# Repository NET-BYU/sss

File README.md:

# Seven Segment Sign

## Welcome to the Seven Segment Sign! (SSS)

## Getting Started
Here are some helpful links to get you up and running!
- [API Docs](https://sss.readthedocs.io/en/latest/API/Display/)
- [Install on Linux/Mac](https://sss.readthedocs.io/en/latest/Installation/Install%20SSS%20on%20Mac%20or%20Linux/)
- [Install on Windows](https://sss.readthedocs.io/en/latest/Installation/Install%20SSS%20on%20Windows/)
- [Create your first demo](https://sss.readthedocs.io/en/latest/Tutorials/Creating%20a%20demo/)

## Common Commands
Although thorough information on how to [get started](https://sss.readthedocs.io/en/latest/Overview/Get%20started/) is in the docs, here are some quick commands you can run in order to get rolling **once you have everything installed**:

- Run the PyGame Simulator for the SSS
  ```bash
  python3 main.py simulator
  ```
- Run a specific demo in the simulator
  ```bash
  python3 main.py demo <demo_name> -s
  ```
- Start the SSS in kiosk mode
  ```bash
  python3 main.py kiosk
  ```
- To view log output of varying degrees, use the `-v` option (the more `v`'s the more `v`erbose the output becomes

For any other help or a list of comprehensive commands, run
```bash
python3 main.py --help
```

## Reporting an Issue
We love feedback! As the SSS codespace expands and acquires new features, we realize that some bugs will fall through the cracks. Please feel free to open a new issue if you notice any bugs in the code, mistakes or missing information in the documentation, or if you want a new feature to be added to the project.

You can go to the **Issues** tab to create a new issue. Please be mindful to choose the correct template for the right type of question. Apart from the currently open issues from before this writing, any **issue that does not conform to the template may become stale or be closed without warning.**

## Submitting a PR
If you are feeling creative and you would like to contribute a demo but you are outside of our organization, you are more than welcome to submit a pull request and we will look it over! 

In order for a pull request to be merged, we have the following three policies:
1. Your code must have adequate, meaningful comments. Don't feel like you have to explain every statement, but also don't write comments like `# This a loop that goes over all the values`.
2. Your PR will need approval from **at least 2 org members**. Users who respond to these the most are @apal6981, @christopolise, and @philipbl
3. Your code **MUST** be formatted with `black`. This is as simple as adding the [Black Formatter](https://marketplace.visualstudio.com/items?itemName=ms-python.black-formatter) to VS/OSS Code or running `python3 -m black <your py files>`

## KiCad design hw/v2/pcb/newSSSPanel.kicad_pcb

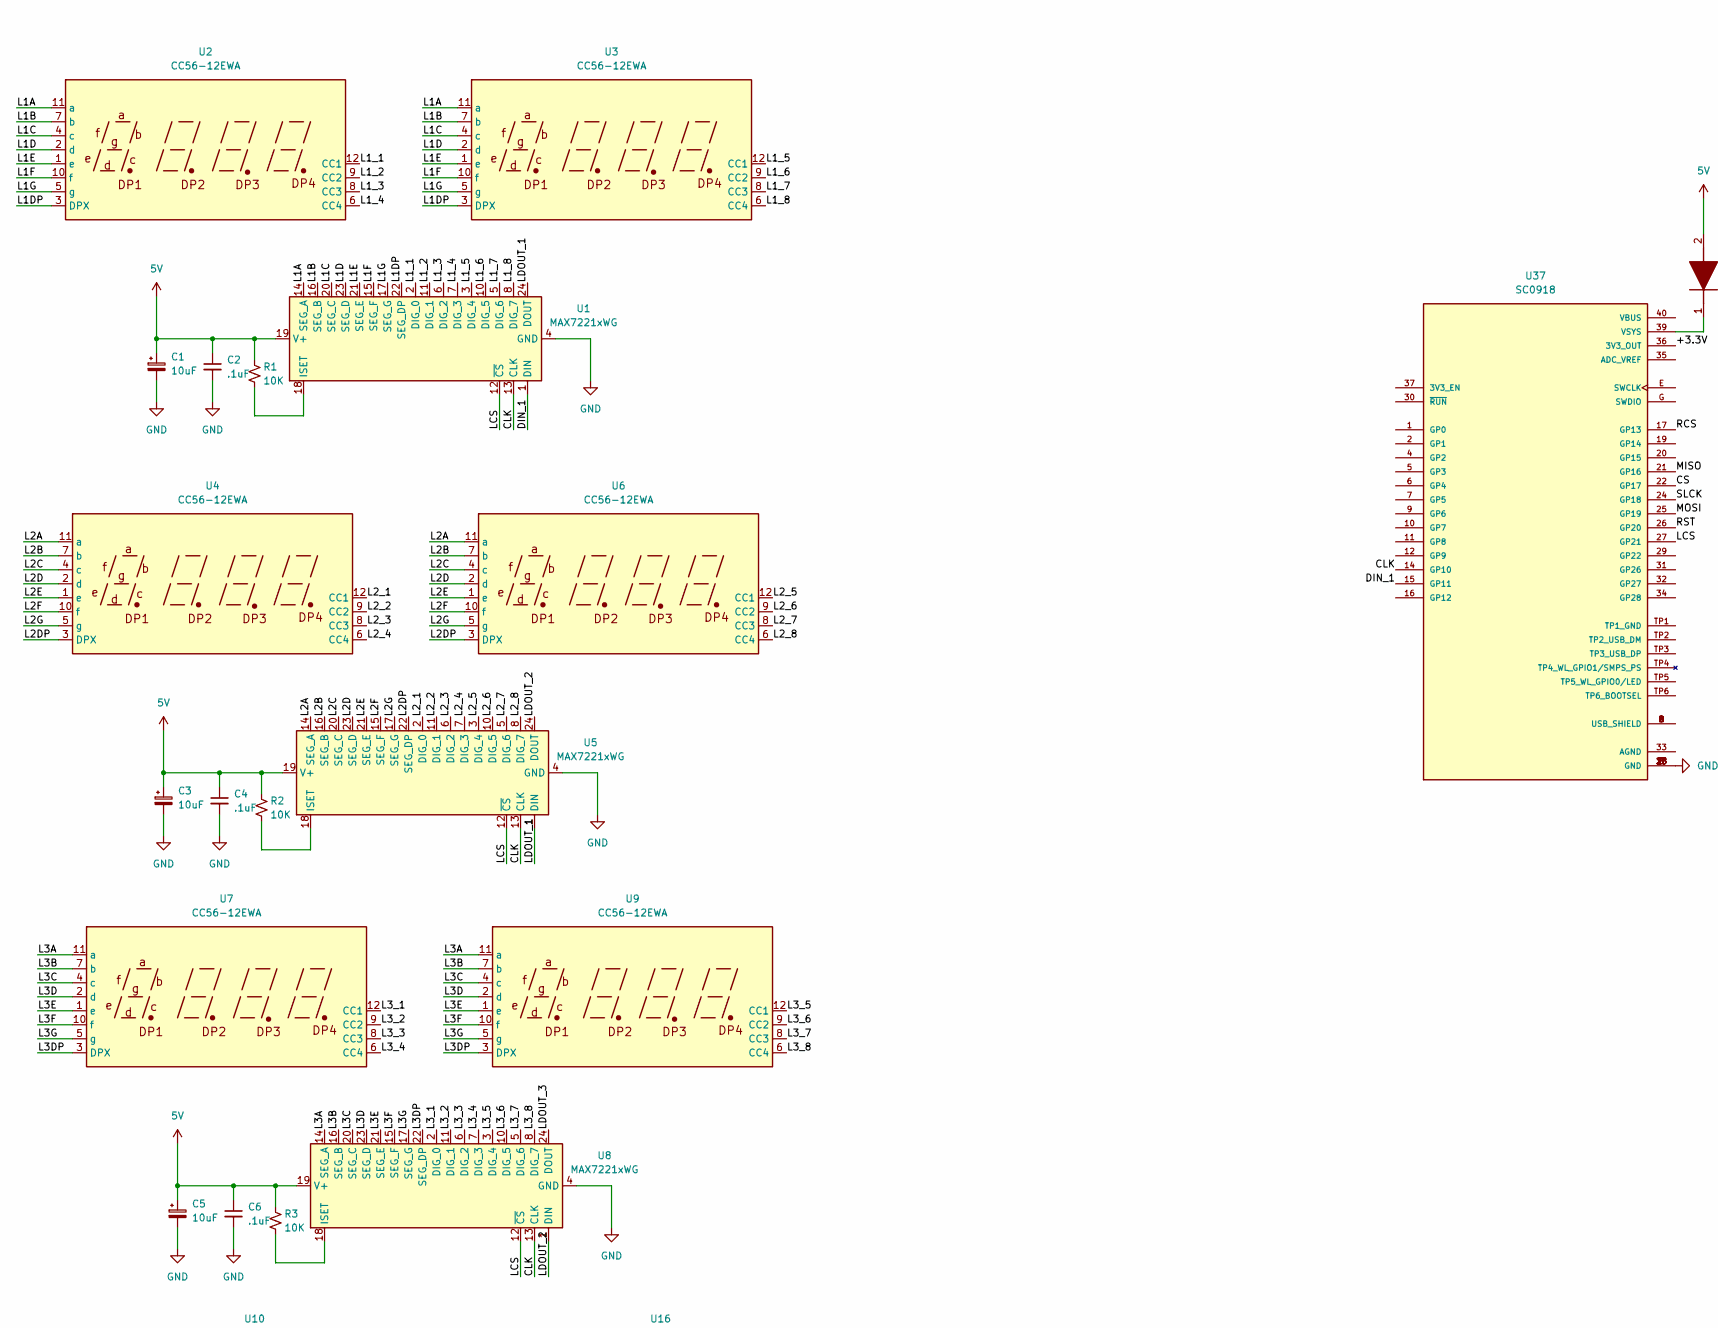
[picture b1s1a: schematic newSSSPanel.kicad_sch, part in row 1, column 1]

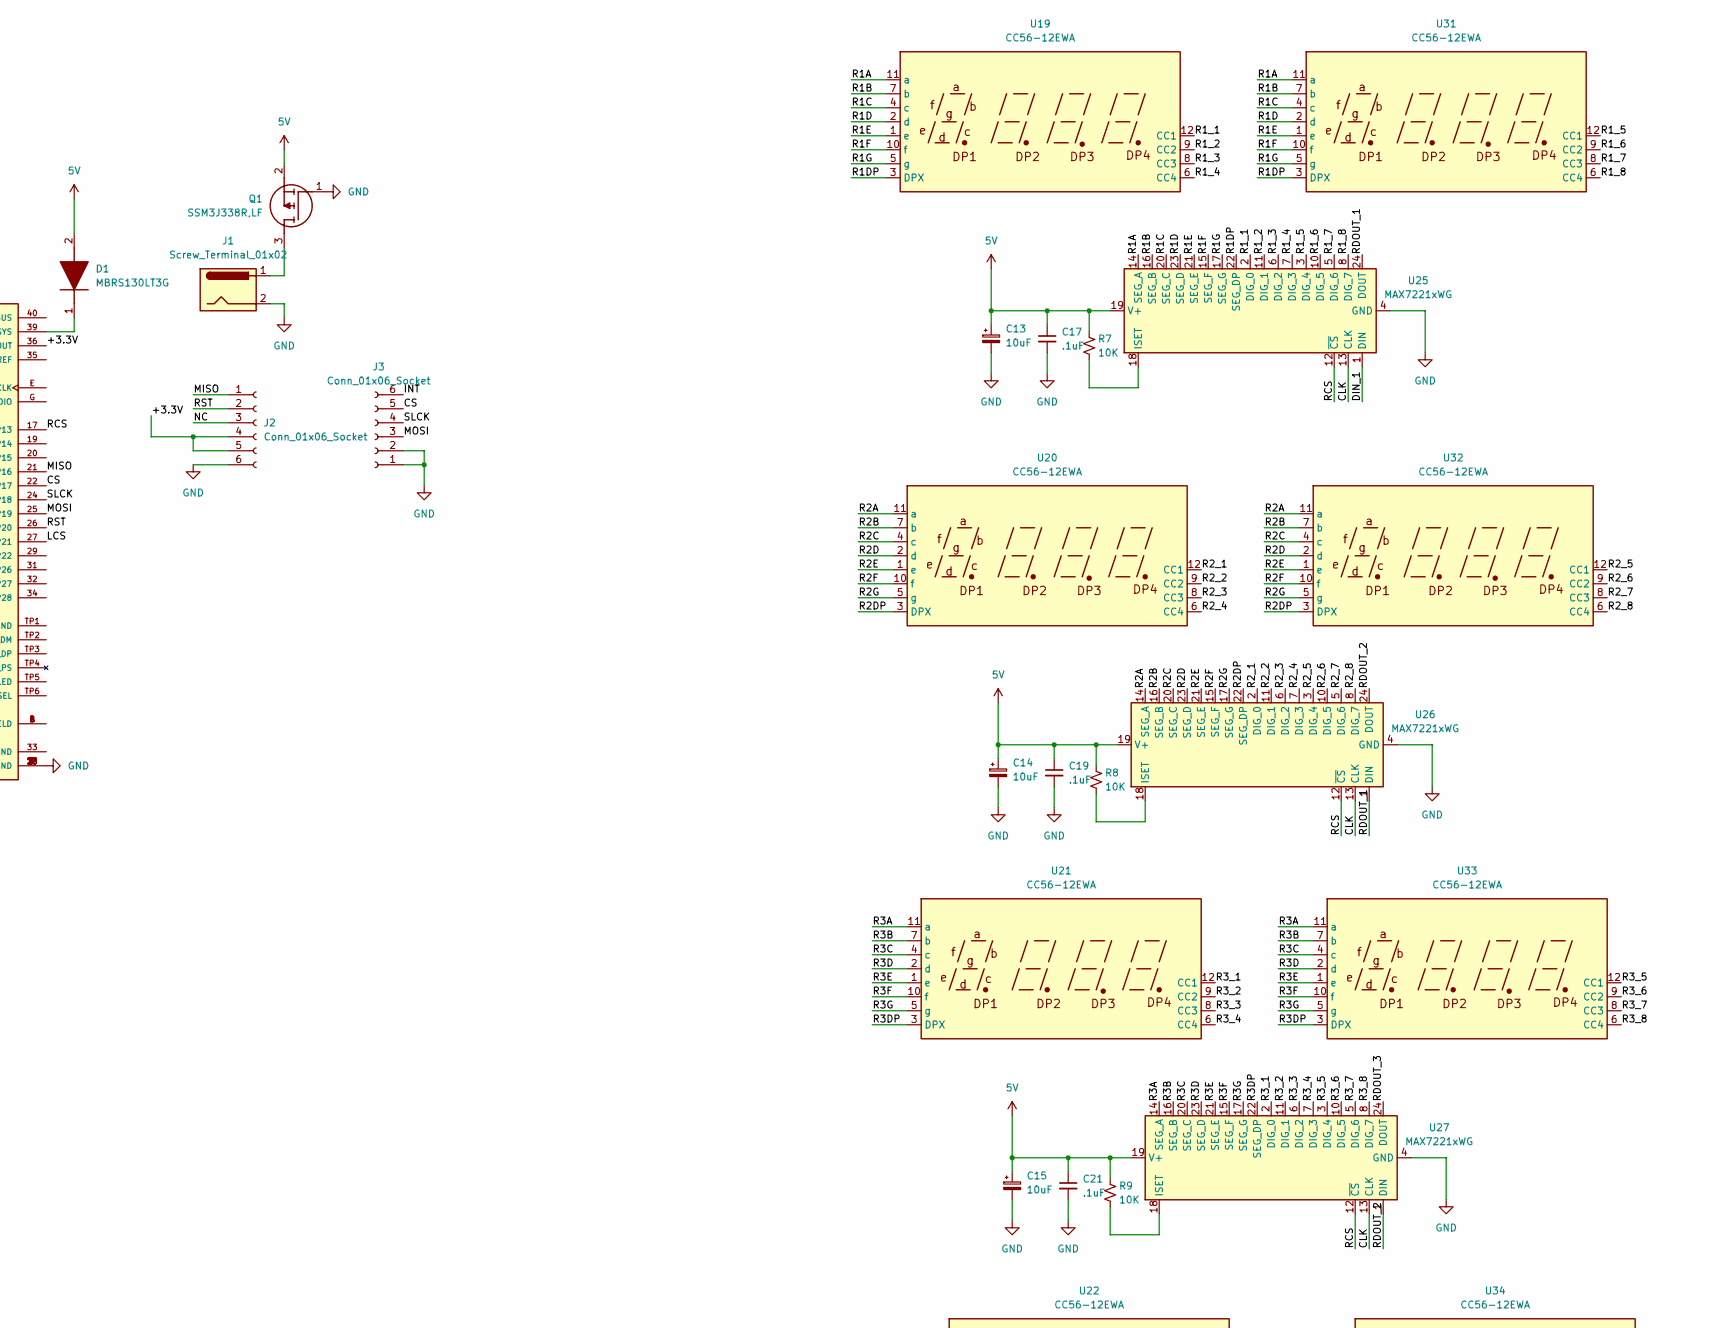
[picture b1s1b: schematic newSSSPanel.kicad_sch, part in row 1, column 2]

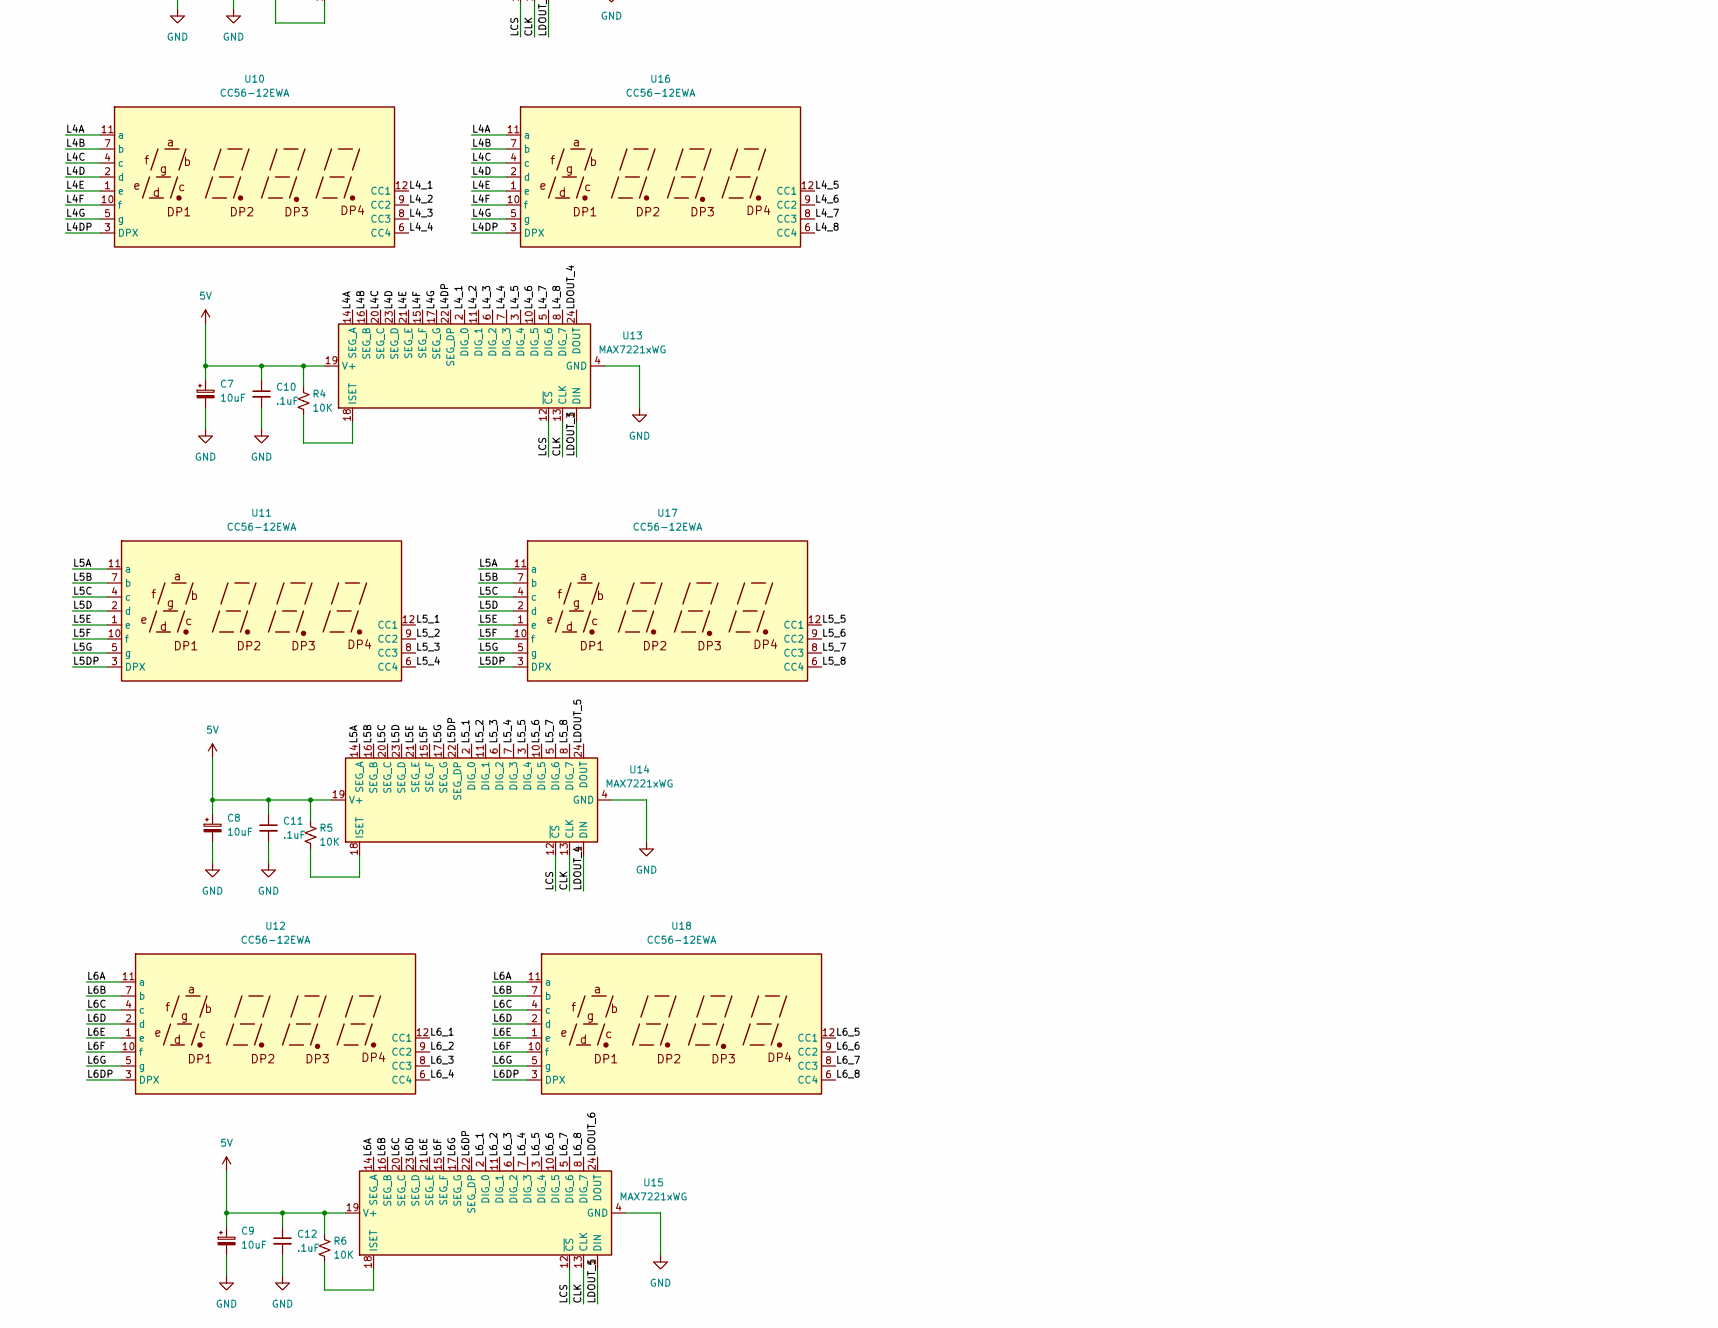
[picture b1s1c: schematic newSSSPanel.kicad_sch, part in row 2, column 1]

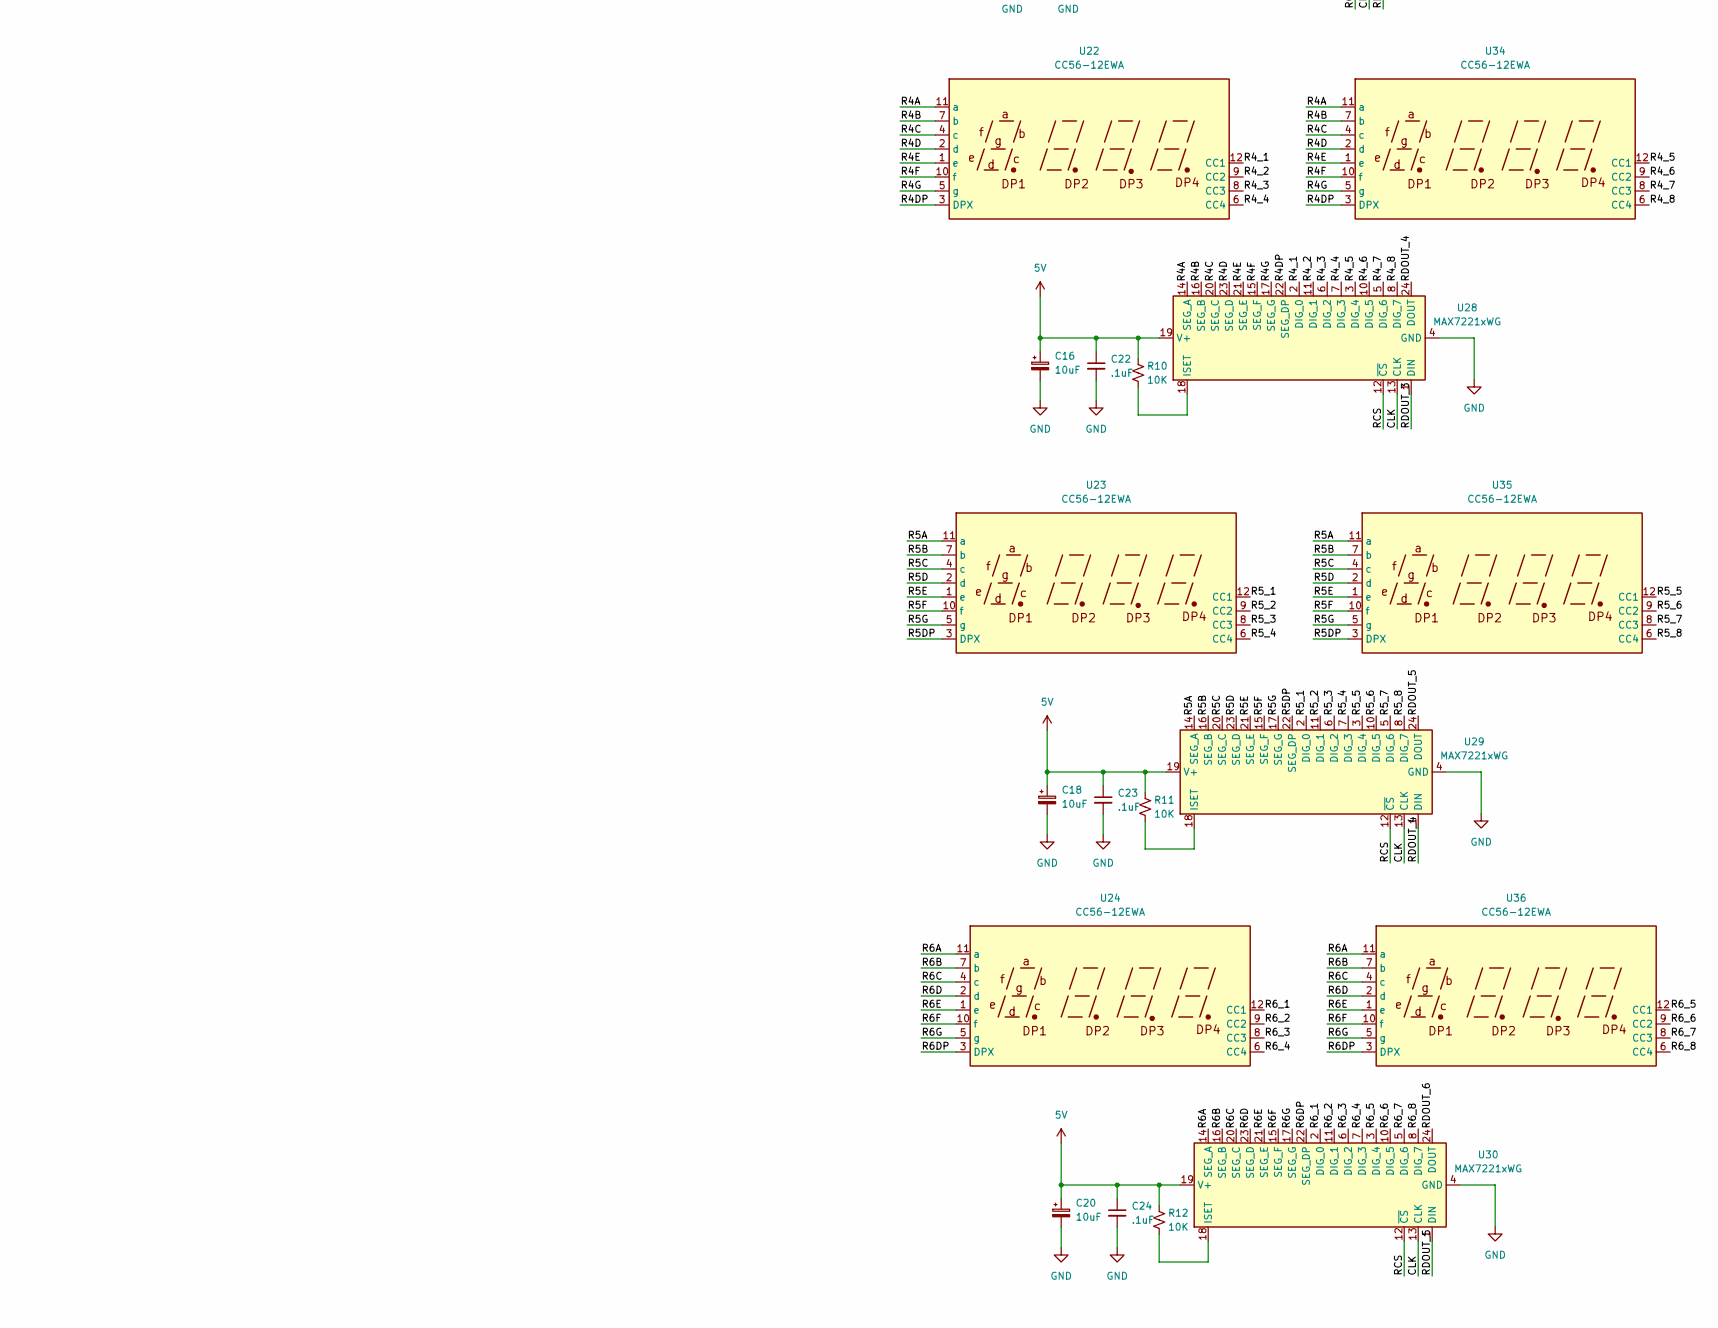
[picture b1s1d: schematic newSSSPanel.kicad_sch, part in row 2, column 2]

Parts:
C1, C3, C5, C7, C8, C9, C13, C14, C15, C16, C18, C20: 10uF; CP_Elec_3x5.4
C2, C4, C6, C10, C11, C12, C17, C19, C21, C22, C23, C24: .1uF; C_0805_2012Metric_Pad1.18x1.45mm_HandSolder
D1: MBRS130LT3G; DIOM5436X247N; Mouser Part Number 863-MBRS130LT3G
J1: Screw_Terminal_01x02; BarrelJack_Horizontal
J2, J3: Conn_01x06_Socket; PinHeader_1x06_P2.54mm_Vertical
Q1: SSM3J338R,LF; SSM3J332RLFT; Mouser Part Number 757-SSM3J338RLF
R1, R2, R3, R4, R5, R6, R7, R8, R9, R10, R11, R12: 10K; R_0805_2012Metric_Pad1.20x1.40mm_HandSolder
U1, U5, U8, U13, U14, U15, U25, U26, U27, U28, U29, U30: MAX7221xWG; SOIC-24W_7.5x15.4mm_P1.27mm
U2, U3, U4, U6, U7, U9, U10, U11, U12, U16, U17, U18, U19, U20, U21, U22, U23, U24, U31, U32, U33, U34, U35, U36: CC56-12EWA; CA56-12EWA
U37: SC0918; MODULE_SC0918; PARTREV 2.1

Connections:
5V: C1.1, C2.1, C3.1, C4.1, C5.1, C6.1, C7.1, C8.1, C9.1, C10.1, C11.1, C12.1, C13.1, C14.1, C15.1, C16.1, C17.1, C18.1, C19.1, C20.1, C21.1, C22.1, C23.1, C24.1, D1.2 (A), Q1.2 (S), R1.1, R2.1, R3.1, R4.1, R5.1, R6.1, R7.1, R8.1, R9.1, R10.1, R11.1, R12.1, U1.19 (V+), U5.19 (V+), U8.19 (V+), U13.19 (V+), U14.19 (V+), U15.19 (V+), U25.19 (V+), U26.19 (V+), U27.19 (V+), U28.19 (V+), U29.19 (V+), U30.19 (V+)
/+3.3V: J2.4, J2.5, U37.36 (3V3_OUT)
/CLK: U1.13 (CLK), U5.13 (CLK), U8.13 (CLK), U13.13 (CLK), U14.13 (CLK), U15.13 (CLK), U25.13 (CLK), U26.13 (CLK), U27.13 (CLK), U28.13 (CLK), U29.13 (CLK), U30.13 (CLK), U37.14 (GP10)
/CS: J3.5, U37.22 (GP17)
/DIN_1: U1.1 (DIN), U25.1 (DIN), U37.15 (GP11)
/INT: J3.6
/L1A: U1.14 (SEG_A), U2.11 (a), U3.11 (a)
/L1B: U1.16 (SEG_B), U2.7 (b), U3.7 (b)
/L1C: U1.20 (SEG_C), U2.4 (c), U3.4 (c)
/L1D: U1.23 (SEG_D), U2.2 (d), U3.2 (d)
/L1DP: U1.22 (SEG_DP), U2.3 (DPX), U3.3 (DPX)
/L1E: U1.21 (SEG_E), U2.1 (e), U3.1 (e)
/L1F: U1.15 (SEG_F), U2.10 (f), U3.10 (f)
/L1G: U1.17 (SEG_G), U2.5 (g), U3.5 (g)
/L1_1: U1.2 (DIG_0), U2.12 (CC1)
/L1_2: U1.11 (DIG_1), U2.9 (CC2)
/L1_3: U1.6 (DIG_2), U2.8 (CC3)
/L1_4: U1.7 (DIG_3), U2.6 (CC4)
/L1_5: U1.3 (DIG_4), U3.12 (CC1)
/L1_6: U1.10 (DIG_5), U3.9 (CC2)
/L1_7: U1.5 (DIG_6), U3.8 (CC3)
/L1_8: U1.8 (DIG_7), U3.6 (CC4)
/L2A: U4.11 (a), U5.14 (SEG_A), U6.11 (a)
/L2B: U4.7 (b), U5.16 (SEG_B), U6.7 (b)
/L2C: U4.4 (c), U5.20 (SEG_C), U6.4 (c)
/L2D: U4.2 (d), U5.23 (SEG_D), U6.2 (d)
/L2DP: U4.3 (DPX), U5.22 (SEG_DP), U6.3 (DPX)
/L2E: U4.1 (e), U5.21 (SEG_E), U6.1 (e)
/L2F: U4.10 (f), U5.15 (SEG_F), U6.10 (f)
/L2G: U4.5 (g), U5.17 (SEG_G), U6.5 (g)
/L2_1: U4.12 (CC1), U5.2 (DIG_0)
/L2_2: U4.9 (CC2), U5.11 (DIG_1)
/L2_3: U4.8 (CC3), U5.6 (DIG_2)
/L2_4: U4.6 (CC4), U5.7 (DIG_3)
/L2_5: U5.3 (DIG_4), U6.12 (CC1)
/L2_6: U5.10 (DIG_5), U6.9 (CC2)
/L2_7: U5.5 (DIG_6), U6.8 (CC3)
/L2_8: U5.8 (DIG_7), U6.6 (CC4)
/L3A: U7.11 (a), U8.14 (SEG_A), U9.11 (a)
/L3B: U7.7 (b), U8.16 (SEG_B), U9.7 (b)
/L3C: U7.4 (c), U8.20 (SEG_C), U9.4 (c)
/L3D: U7.2 (d), U8.23 (SEG_D), U9.2 (d)
/L3DP: U7.3 (DPX), U8.22 (SEG_DP), U9.3 (DPX)
/L3E: U7.1 (e), U8.21 (SEG_E), U9.1 (e)
/L3F: U7.10 (f), U8.15 (SEG_F), U9.10 (f)
/L3G: U7.5 (g), U8.17 (SEG_G), U9.5 (g)
/L3_1: U7.12 (CC1), U8.2 (DIG_0)
/L3_2: U7.9 (CC2), U8.11 (DIG_1)
/L3_3: U7.8 (CC3), U8.6 (DIG_2)
/L3_4: U7.6 (CC4), U8.7 (DIG_3)
/L3_5: U8.3 (DIG_4), U9.12 (CC1)
/L3_6: U8.10 (DIG_5), U9.9 (CC2)
/L3_7: U8.5 (DIG_6), U9.8 (CC3)
/L3_8: U8.8 (DIG_7), U9.6 (CC4)
/L4A: U10.11 (a), U13.14 (SEG_A), U16.11 (a)
/L4B: U10.7 (b), U13.16 (SEG_B), U16.7 (b)
/L4C: U10.4 (c), U13.20 (SEG_C), U16.4 (c)
/L4D: U10.2 (d), U13.23 (SEG_D), U16.2 (d)
/L4DP: U10.3 (DPX), U13.22 (SEG_DP), U16.3 (DPX)
/L4E: U10.1 (e), U13.21 (SEG_E), U16.1 (e)
/L4F: U10.10 (f), U13.15 (SEG_F), U16.10 (f)
/L4G: U10.5 (g), U13.17 (SEG_G), U16.5 (g)
/L4_1: U10.12 (CC1), U13.2 (DIG_0)
/L4_2: U10.9 (CC2), U13.11 (DIG_1)
/L4_3: U10.8 (CC3), U13.6 (DIG_2)
/L4_4: U10.6 (CC4), U13.7 (DIG_3)
/L4_5: U13.3 (DIG_4), U16.12 (CC1)
/L4_6: U13.10 (DIG_5), U16.9 (CC2)
/L4_7: U13.5 (DIG_6), U16.8 (CC3)
/L4_8: U13.8 (DIG_7), U16.6 (CC4)
/L5A: U11.11 (a), U14.14 (SEG_A), U17.11 (a)
/L5B: U11.7 (b), U14.16 (SEG_B), U17.7 (b)
/L5C: U11.4 (c), U14.20 (SEG_C), U17.4 (c)
/L5D: U11.2 (d), U14.23 (SEG_D), U17.2 (d)
/L5DP: U11.3 (DPX), U14.22 (SEG_DP), U17.3 (DPX)
/L5E: U11.1 (e), U14.21 (SEG_E), U17.1 (e)
/L5F: U11.10 (f), U14.15 (SEG_F), U17.10 (f)
/L5G: U11.5 (g), U14.17 (SEG_G), U17.5 (g)
/L5_1: U11.12 (CC1), U14.2 (DIG_0)
/L5_2: U11.9 (CC2), U14.11 (DIG_1)
/L5_3: U11.8 (CC3), U14.6 (DIG_2)
/L5_4: U11.6 (CC4), U14.7 (DIG_3)
/L5_5: U14.3 (DIG_4), U17.12 (CC1)
/L5_6: U14.10 (DIG_5), U17.9 (CC2)
/L5_7: U14.5 (DIG_6), U17.8 (CC3)
/L5_8: U14.8 (DIG_7), U17.6 (CC4)
/L6A: U12.11 (a), U15.14 (SEG_A), U18.11 (a)
/L6B: U12.7 (b), U15.16 (SEG_B), U18.7 (b)
/L6C: U12.4 (c), U15.20 (SEG_C), U18.4 (c)
/L6D: U12.2 (d), U15.23 (SEG_D), U18.2 (d)
/L6DP: U12.3 (DPX), U15.22 (SEG_DP), U18.3 (DPX)
/L6E: U12.1 (e), U15.21 (SEG_E), U18.1 (e)
/L6F: U12.10 (f), U15.15 (SEG_F), U18.10 (f)
/L6G: U12.5 (g), U15.17 (SEG_G), U18.5 (g)
/L6_1: U12.12 (CC1), U15.2 (DIG_0)
/L6_2: U12.9 (CC2), U15.11 (DIG_1)
/L6_3: U12.8 (CC3), U15.6 (DIG_2)
/L6_4: U12.6 (CC4), U15.7 (DIG_3)
/L6_5: U15.3 (DIG_4), U18.12 (CC1)
/L6_6: U15.10 (DIG_5), U18.9 (CC2)
/L6_7: U15.5 (DIG_6), U18.8 (CC3)
/L6_8: U15.8 (DIG_7), U18.6 (CC4)
/LCS: U1.12 (~CS), U5.12 (~CS), U8.12 (~CS), U13.12 (~CS), U14.12 (~CS), U15.12 (~CS), U37.27 (GP21)
/LDOUT_1: U1.24 (DOUT), U5.1 (DIN)
/LDOUT_2: U5.24 (DOUT), U8.1 (DIN)
/LDOUT_3: U8.24 (DOUT), U13.1 (DIN)
/LDOUT_4: U13.24 (DOUT), U14.1 (DIN)
/LDOUT_5: U14.24 (DOUT), U15.1 (DIN)
/LDOUT_6: U15.24 (DOUT)
/MISO: J2.1, U37.21 (GP16)
/MOSI: J3.3, U37.25 (GP19)
/NC: J2.3
/R1A: U19.11 (a), U25.14 (SEG_A), U31.11 (a)
/R1B: U19.7 (b), U25.16 (SEG_B), U31.7 (b)
/R1C: U19.4 (c), U25.20 (SEG_C), U31.4 (c)
/R1D: U19.2 (d), U25.23 (SEG_D), U31.2 (d)
/R1DP: U19.3 (DPX), U25.22 (SEG_DP), U31.3 (DPX)
/R1E: U19.1 (e), U25.21 (SEG_E), U31.1 (e)
/R1F: U19.10 (f), U25.15 (SEG_F), U31.10 (f)
/R1G: U19.5 (g), U25.17 (SEG_G), U31.5 (g)
/R1_1: U19.12 (CC1), U25.2 (DIG_0)
/R1_2: U19.9 (CC2), U25.11 (DIG_1)
/R1_3: U19.8 (CC3), U25.6 (DIG_2)
/R1_4: U19.6 (CC4), U25.7 (DIG_3)
/R1_5: U25.3 (DIG_4), U31.12 (CC1)
/R1_6: U25.10 (DIG_5), U31.9 (CC2)
/R1_7: U25.5 (DIG_6), U31.8 (CC3)
/R1_8: U25.8 (DIG_7), U31.6 (CC4)
/R2A: U20.11 (a), U26.14 (SEG_A), U32.11 (a)
/R2B: U20.7 (b), U26.16 (SEG_B), U32.7 (b)
/R2C: U20.4 (c), U26.20 (SEG_C), U32.4 (c)
/R2D: U20.2 (d), U26.23 (SEG_D), U32.2 (d)
/R2DP: U20.3 (DPX), U26.22 (SEG_DP), U32.3 (DPX)
/R2E: U20.1 (e), U26.21 (SEG_E), U32.1 (e)
/R2F: U20.10 (f), U26.15 (SEG_F), U32.10 (f)
/R2G: U20.5 (g), U26.17 (SEG_G), U32.5 (g)
/R2_1: U20.12 (CC1), U26.2 (DIG_0)
/R2_2: U20.9 (CC2), U26.11 (DIG_1)
/R2_3: U20.8 (CC3), U26.6 (DIG_2)
/R2_4: U20.6 (CC4), U26.7 (DIG_3)
/R2_5: U26.3 (DIG_4), U32.12 (CC1)
/R2_6: U26.10 (DIG_5), U32.9 (CC2)
/R2_7: U26.5 (DIG_6), U32.8 (CC3)
/R2_8: U26.8 (DIG_7), U32.6 (CC4)
/R3A: U21.11 (a), U27.14 (SEG_A), U33.11 (a)
/R3B: U21.7 (b), U27.16 (SEG_B), U33.7 (b)
/R3C: U21.4 (c), U27.20 (SEG_C), U33.4 (c)
/R3D: U21.2 (d), U27.23 (SEG_D), U33.2 (d)
/R3DP: U21.3 (DPX), U27.22 (SEG_DP), U33.3 (DPX)
/R3E: U21.1 (e), U27.21 (SEG_E), U33.1 (e)
/R3F: U21.10 (f), U27.15 (SEG_F), U33.10 (f)
/R3G: U21.5 (g), U27.17 (SEG_G), U33.5 (g)
/R3_1: U21.12 (CC1), U27.2 (DIG_0)
/R3_2: U21.9 (CC2), U27.11 (DIG_1)
/R3_3: U21.8 (CC3), U27.6 (DIG_2)
/R3_4: U21.6 (CC4), U27.7 (DIG_3)
/R3_5: U27.3 (DIG_4), U33.12 (CC1)
/R3_6: U27.10 (DIG_5), U33.9 (CC2)
/R3_7: U27.5 (DIG_6), U33.8 (CC3)
/R3_8: U27.8 (DIG_7), U33.6 (CC4)
/R4A: U22.11 (a), U28.14 (SEG_A), U34.11 (a)
/R4B: U22.7 (b), U28.16 (SEG_B), U34.7 (b)
/R4C: U22.4 (c), U28.20 (SEG_C), U34.4 (c)
/R4D: U22.2 (d), U28.23 (SEG_D), U34.2 (d)
/R4DP: U22.3 (DPX), U28.22 (SEG_DP), U34.3 (DPX)
/R4E: U22.1 (e), U28.21 (SEG_E), U34.1 (e)
/R4F: U22.10 (f), U28.15 (SEG_F), U34.10 (f)
/R4G: U22.5 (g), U28.17 (SEG_G), U34.5 (g)
/R4_1: U22.12 (CC1), U28.2 (DIG_0)
/R4_2: U22.9 (CC2), U28.11 (DIG_1)
/R4_3: U22.8 (CC3), U28.6 (DIG_2)
/R4_4: U22.6 (CC4), U28.7 (DIG_3)
/R4_5: U28.3 (DIG_4), U34.12 (CC1)
/R4_6: U28.10 (DIG_5), U34.9 (CC2)
/R4_7: U28.5 (DIG_6), U34.8 (CC3)
/R4_8: U28.8 (DIG_7), U34.6 (CC4)
/R5A: U23.11 (a), U29.14 (SEG_A), U35.11 (a)
/R5B: U23.7 (b), U29.16 (SEG_B), U35.7 (b)
/R5C: U23.4 (c), U29.20 (SEG_C), U35.4 (c)
/R5D: U23.2 (d), U29.23 (SEG_D), U35.2 (d)
/R5DP: U23.3 (DPX), U29.22 (SEG_DP), U35.3 (DPX)
/R5E: U23.1 (e), U29.21 (SEG_E), U35.1 (e)
/R5F: U23.10 (f), U29.15 (SEG_F), U35.10 (f)
/R5G: U23.5 (g), U29.17 (SEG_G), U35.5 (g)
/R5_1: U23.12 (CC1), U29.2 (DIG_0)
/R5_2: U23.9 (CC2), U29.11 (DIG_1)
/R5_3: U23.8 (CC3), U29.6 (DIG_2)
/R5_4: U23.6 (CC4), U29.7 (DIG_3)
/R5_5: U29.3 (DIG_4), U35.12 (CC1)
/R5_6: U29.10 (DIG_5), U35.9 (CC2)
/R5_7: U29.5 (DIG_6), U35.8 (CC3)
/R5_8: U29.8 (DIG_7), U35.6 (CC4)
/R6A: U24.11 (a), U30.14 (SEG_A), U36.11 (a)
/R6B: U24.7 (b), U30.16 (SEG_B), U36.7 (b)
/R6C: U24.4 (c), U30.20 (SEG_C), U36.4 (c)
/R6D: U24.2 (d), U30.23 (SEG_D), U36.2 (d)
/R6DP: U24.3 (DPX), U30.22 (SEG_DP), U36.3 (DPX)
/R6E: U24.1 (e), U30.21 (SEG_E), U36.1 (e)
/R6F: U24.10 (f), U30.15 (SEG_F), U36.10 (f)
/R6G: U24.5 (g), U30.17 (SEG_G), U36.5 (g)
/R6_1: U24.12 (CC1), U30.2 (DIG_0)
/R6_2: U24.9 (CC2), U30.11 (DIG_1)
/R6_3: U24.8 (CC3), U30.6 (DIG_2)
/R6_4: U24.6 (CC4), U30.7 (DIG_3)
/R6_5: U30.3 (DIG_4), U36.12 (CC1)
/R6_6: U30.10 (DIG_5), U36.9 (CC2)
/R6_7: U30.5 (DIG_6), U36.8 (CC3)
/R6_8: U30.8 (DIG_7), U36.6 (CC4)
/RCS: U25.12 (~CS), U26.12 (~CS), U27.12 (~CS), U28.12 (~CS), U29.12 (~CS), U30.12 (~CS), U37.17 (GP13)
/RDOUT_1: U25.24 (DOUT), U26.1 (DIN)
/RDOUT_2: U26.24 (DOUT), U27.1 (DIN)
/RDOUT_3: U27.24 (DOUT), U28.1 (DIN)
/RDOUT_4: U28.24 (DOUT), U29.1 (DIN)
/RDOUT_5: U29.24 (DOUT), U30.1 (DIN)
/RDOUT_6: U30.24 (DOUT)
/RST: J2.2, U37.26 (GP20)
/SLCK: J3.4, U37.24 (GP18)
GND: C1.2, C2.2, C3.2, C4.2, C5.2, C6.2, C7.2, C8.2, C9.2, C10.2, C11.2, C12.2, C13.2, C14.2, C15.2, C16.2, C17.2, C18.2, C19.2, C20.2, C21.2, C22.2, C23.2, C24.2, J1.2, J2.6, J3.1, J3.2, Q1.1 (G), U1.4 (GND), U1.9 (GND), U5.4 (GND), U5.9 (GND), U8.4 (GND), U8.9 (GND), U13.4 (GND), U13.9 (GND), U14.4 (GND), U14.9 (GND), U15.4 (GND), U15.9 (GND), U25.4 (GND), U25.9 (GND), U26.4 (GND), U26.9 (GND), U27.4 (GND), U27.9 (GND), U28.4 (GND), U28.9 (GND), U29.4 (GND), U29.9 (GND), U30.4 (GND), U30.9 (GND), U37.3 (GND), U37.8 (GND), U37.13 (GND), U37.18 (GND), U37.23 (GND), U37.28 (GND), U37.38 (GND), U37.F (GND)
unnamed: D1.1 (K), U37.39 (VSYS)
unnamed: J1.1, Q1.3 (D)
unnamed: R1.2, U1.18 (ISET)
unnamed: R2.2, U5.18 (ISET)
unnamed: R3.2, U8.18 (ISET)
unnamed: R4.2, U13.18 (ISET)
unnamed: R5.2, U14.18 (ISET)
unnamed: R6.2, U15.18 (ISET)
unnamed: R7.2, U25.18 (ISET)
unnamed: R8.2, U26.18 (ISET)
unnamed: R9.2, U27.18 (ISET)
unnamed: R10.2, U28.18 (ISET)
unnamed: R11.2, U29.18 (ISET)
unnamed: R12.2, U30.18 (ISET)

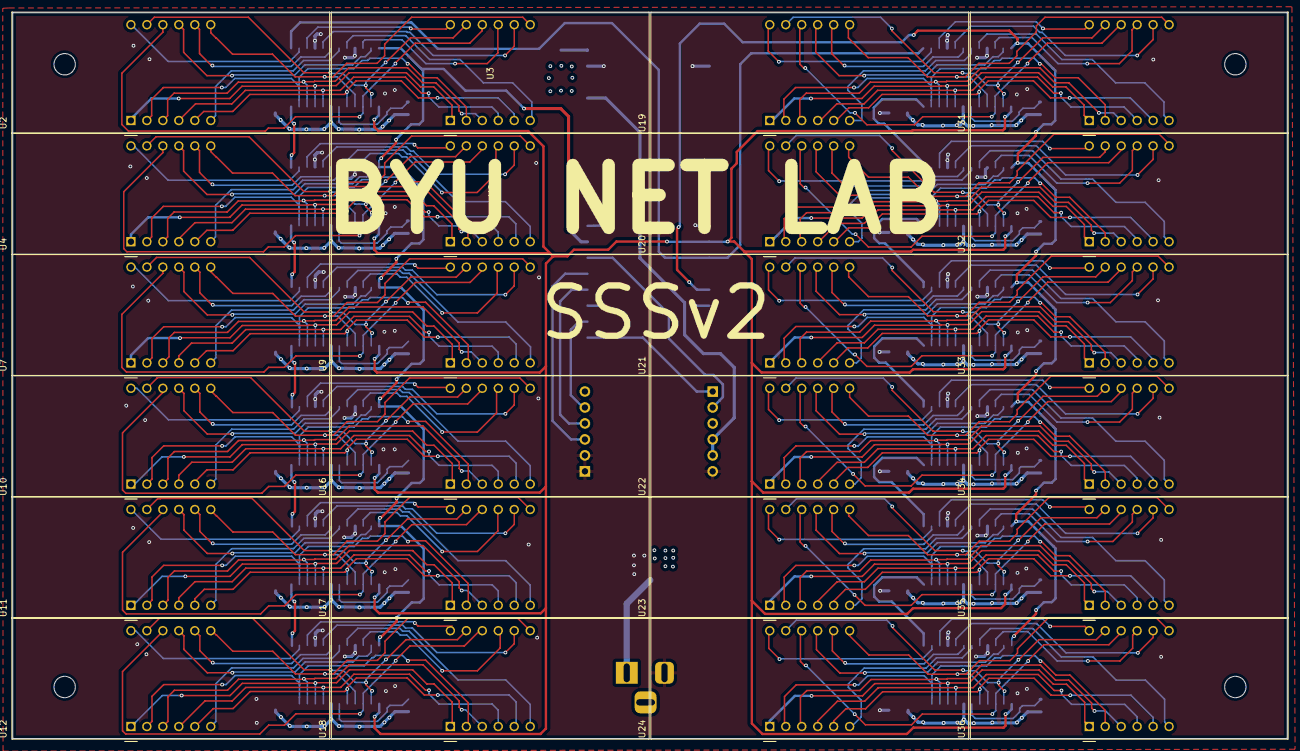
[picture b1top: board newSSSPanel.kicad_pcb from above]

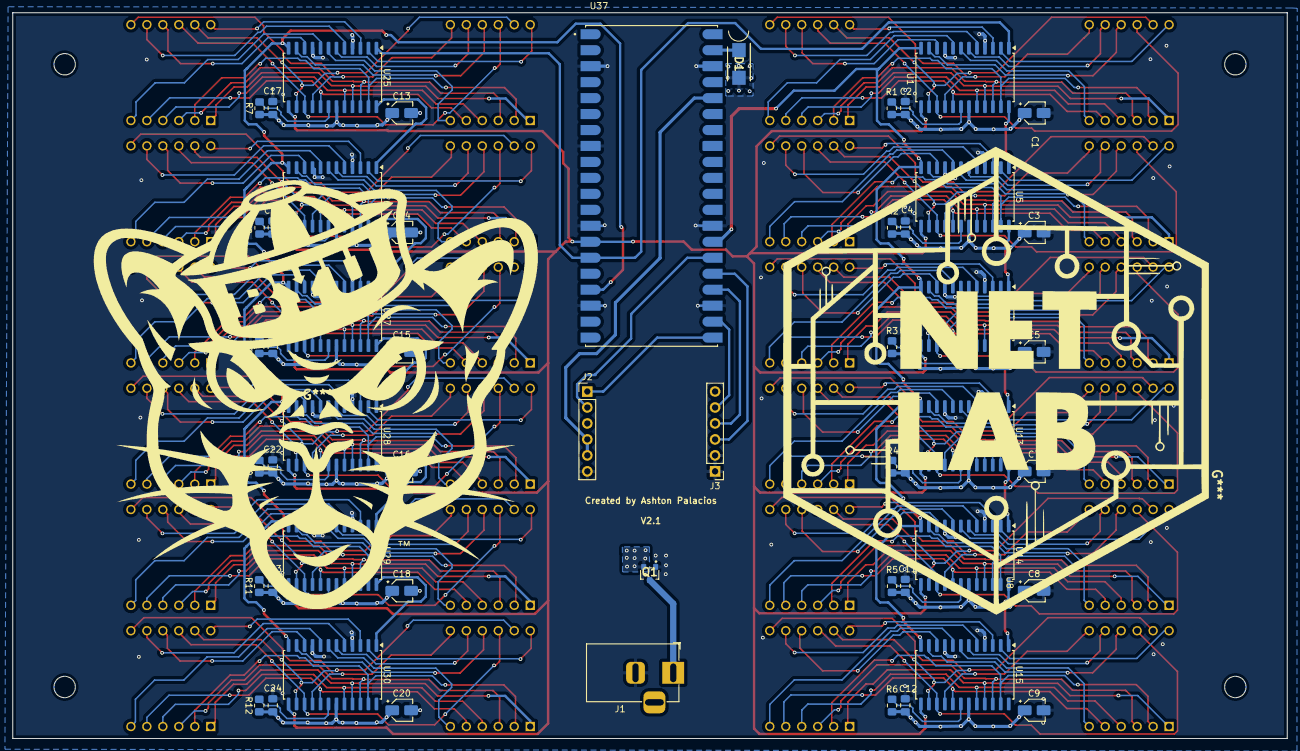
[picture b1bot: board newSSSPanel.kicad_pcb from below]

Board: 4 copper layers, 202.7 x 115.4 mm, 78 parts (54 on the bottom side), 228 nets.

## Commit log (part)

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2022-06-27 Fix bug in kiosk with setting demo time
2022-06-27 Fixing 'NO CAMERA' being stuck on the screen
2022-06-28 Format all code using black
2022-06-28 Hotfix for requirements.txt
2022-06-28 Remove comments of testing
2022-06-28 Testing error type
2022-06-28 Clean up requirements
2022-06-28 Move import error and disable keyboard
2022-06-29 Move try except to keyboard.py
2022-06-29 Return none to disable keyboard
2022-06-29 Cleanup log output
2022-06-30 Add self-hosted action to check on a Raspberry Pi
    This will run the test suite on the Raspberry Pi to make sure it runs
    properly on the correct hardware.
2022-06-30 Improve testing script
2022-06-30 Camera punished
2022-06-30 Add pylint configuration file
2022-06-30 Fix error with importing pygame
    Moved imports around so that pygame is not accidentally imported when
    running tests.
2022-07-01 Hold on
2022-07-01 No one wants this
2022-07-05 Refresh display between user selected demos
2022-07-05 fixed restarting bug
2022-07-05 fixing up the snake game and snake ai demo
2022-07-05 changed logger statements to debug status
2022-07-05 reran black, setting line length to 100 did weird things upstream
2022-07-06 Add keymap for more buttons, added output stream from doom
2022-07-06 Enable output logging
2022-07-07 Added broadcaster module
2022-07-07 Fix logic behind reading queue
2022-07-07 Checked in kiosk and fixed ai
2022-07-07 No broadcasters for simulator...ask @apal6981
2022-07-07 Start game and manage the memory
2022-07-07 Readme cleanup
2022-07-07 Now will avoid looking for a camera that is disconnected
2022-07-08 Add verbose flag to CLI
2022-07-08 Specify sysv-ipc version
2022-07-08 Guard statement instead of static while
2022-07-08 Added an interesting level
2022-07-08 Better lighting levels
2022-07-08 Different color sorting
2022-07-08 Better WAD
2022-07-09 Remove line from simulator
2022-07-09 Fix style of passing out message to broadcasters
2022-07-11 Add isort to formatting action
2022-07-12 Handle keyboard interrupts
2022-07-12 Refactor
2022-07-12 Refactor code
    Put Queues data class into utils
2022-07-14 Update theme and requirements
2022-07-14 Start of intro
2022-07-14 Intro is landing?
2022-07-14 Fix intro and add support
2022-07-14 Fixed light-dark mode toggle
2022-07-14 Fix html injection line
2022-07-19 Clear screen after stopping demo
2022-07-19 Handle keyboard interrupt in simulator
2022-07-28 Suppress game output, status message for end added
2022-08-10 Some comments and docs for installing
2022-08-10 about the team
2022-08-12 Add device tree assets
2022-08-12 Finished GPIO article
2022-08-12 Another method
2022-08-12 Its not pretty but there it is
2022-08-12 Reorganize hardwire files
2022-08-12 Finished camera documentation
2022-08-12 Finished enclosure and feet sans 3mf
2022-08-12 More schematics and brd images added
2022-08-13 Finished FAQs
2022-08-13 Transparency images fixed
2022-08-16 Panel article
2022-08-16 Panels
2022-08-17 Windows notes
2022-08-18 Set default version to latest with mike 1.1.2
2022-08-18 Test versioning
2022-08-18 Added dropdown
2022-08-18 Remove hard ref
2022-08-18 restart sss rtfd
2022-08-18 Update to incorporate sss rtfd
2022-09-01 Hotfix that prevents issue #25
2022-09-08 Handle exceptions when playing demo in kiosk mode
2023-03-15 News section in docs
2023-03-21 test formatting
2023-03-21 reformat offending files
2023-03-21 Forgot some
2023-05-05 Basic draft with multiple screens of definitions
2023-05-05 Tweaked output format
2023-05-05 Added definitions
2023-05-24 Update news
2023-06-09 Added new link and removed site folder tracking
2023-06-13 Recursive zero finding works
2023-06-13 Added flag drawing logic
2023-06-14 Game win/lose logic set. Pending repeat direction arrows
2023-06-14 Fix game over logic
2023-08-21 init of two_circle
2023-08-22 Added new code for a two pixel circle display, to a new branch
2023-08-24 Clarify virtual environment indicator
2023-08-24 Fix internal link #33
2023-08-24 Fix comments to be compatible with mkdocstring #34
2023-08-25 Add some new comments
2023-08-25 Decided to split movement into separate functions. made a new branch
2023-08-28 single panel debug
2023-08-28 More detailed and formatted docs for broadcasters and controllers
2023-08-29 fixed the demo and some print statements
2023-08-29 removed the asdf from video demo
2023-08-30 Some work done, still struggling
2023-08-30 Yes, this is bad juju, but it fixes the build
2023-08-30 Fix format issue
2023-08-30 Added shrek and better formatting
2023-08-30 Debug again
2023-08-30 Found the bugger
2023-08-31 Hot mess
2023-08-31 Debug drawing speed
2023-08-31 Trying to fit formatting requirements better
2023-08-31 Fix formatting
2023-08-31 Fix formatting ++
2023-08-31 init
2023-08-31 Adding pygame-mixer sound broadcaster
2023-08-31 Update issue templates
    This provides templates to make it easier for users/developers to describe what is going wrong and how it can be addressed
2023-08-31 Some sounds don't work, removing them
2023-09-01 Fixing formatting
2023-09-01 Fixing slight sound delay
2023-09-01 Snake sounds
2023-09-01 Adding a ton of new sounds
2023-09-01 Fixed skipping videos that have already been processed'
2023-09-01 Fixing and adding some things
2023-09-01 Formatting welcome_y
2023-09-01 creating a place for bryson to work his magic
2023-09-01 Adding sully sound
2023-09-01 Tetris clear row sound
2023-09-01 added sounds to movement
2023-09-01 Adding Nyan Cat sound
2023-09-01 Formatting video sound
2023-09-01 Quic under_construction
2023-09-01 Rick was having some issues but I fixed them
2023-10-18 Bump urllib3 from 1.26.9 to 1.26.18
    Bumps [urllib3](https://github.com/urllib3/urllib3) from 1.26.9 to 1.26.18.
    - [Release notes](https://github.com/urllib3/urllib3/releases)
    - [Changelog](https://github.com/urllib3/urllib3/blob/main/CHANGES.rst)
    - [Commits](https://github.com/urllib3/urllib3/compare/1.26.9...1.26.18)
    ---
    updated-dependencies:
2024-04-12 Adding a few sounds
2024-08-19 Fixing minor issue in hangman_ai, changing is_not to != to remove warning
2024-08-19 Bump black from 22.6.0 to 24.3.0
    Bumps [black](https://github.com/psf/black) from 22.6.0 to 24.3.0.
    - [Release notes](https://github.com/psf/black/releases)
    - [Changelog](https://github.com/psf/black/blob/main/CHANGES.md)
    - [Commits](https://github.com/psf/black/compare/22.6.0...24.3.0)
    ---
    updated-dependencies:
2024-08-19 Run formatter
2024-08-19 Maze builds alright
2024-08-19 Main gameplay is working
2024-08-19 Trying to use sounds with maze
2024-08-20 Working on prints
2024-08-23 Figure out python environment
2024-08-23 Test something else out
2024-08-23 Try more stuff
2024-08-23 More stuff
2024-08-31 Bump opencv-python from 4.6.0.66 to 4.8.1.78
    Bumps [opencv-python](https://github.com/opencv/opencv-python) from 4.6.0.66 to 4.8.1.78.
    - [Release notes](https://github.com/opencv/opencv-python/releases)
    - [Commits](https://github.com/opencv/opencv-python/commits)
    ---
    updated-dependencies:
    - dependency-name: opencv-python
2024-10-22 Fix ai stuck in loop
2024-10-22 Fix import sorting
2024-10-22 Fix formatting and comments
2024-10-23 Try to set up python version
2024-10-23 More testing
2024-10-23 Keep on fixing...
2024-10-23 Test normal tester
2024-10-23 Fix problem with using pyenv
2024-10-23 Update openCV
2024-10-23 Update pyyaml
2024-10-23 Test more python versions
2024-10-23 Update versions of actions
2024-10-23 Raise more descriptive error when text is too long
    Fixes #36
2024-10-23 Added docstrings for pretty much everything
2024-10-23 Fixed tetris error
2024-10-23 Fixed circle error
2024-10-23 Make a little cleaner
2024-10-23 Lets try this again
2024-10-23 Update rules hotfix
2024-10-23 Maybe this will help
2024-10-23 Pkt upgrades
2024-10-23 I'm getting lazier
2024-10-23 I'm so done with this junk
2024-10-23 Added runner docs
2024-10-23 Reformat with isort
2024-10-23 Fix isort issues
2024-10-24 Fix @philipbl knitpick
2024-10-24 hotfix to snake ai crashing and not displaying a banner when restarting
2024-10-25 Only print logs if controllers are there
2024-10-25 Fix logo placement for flag as ref'd in #67
2024-10-25 Add sound broadcaster
2024-10-25 Fix imports
2024-10-25 Fix the order of the demos
2024-10-31 adding v2 hardware
2024-10-31 formatted
2024-10-31 cleaned up some constants and comments
2024-10-31 Add initial menu system while in kiosk mode
2024-10-31 Fix problem with breakout taking all input from q
2024-10-31 Change the button to select the demo
2024-10-31 Center title
2024-11-01 changed dependency on pygame, only loads when screen is being simulated
2024-11-01 formated with black
2024-11-01 Fix typo
2024-11-01 Change the way transitions happen between menu
    Previously I was detecting items in the demo queue. I changed it to
    detect SEL or SEC in the system queue. This made the logic way eaiser.
2024-11-01 Change to a better trigger key press
2024-11-01 renamed files and newhardware variable -> new_hardware
2024-11-03 Handle if the system input queue is not provided
2024-11-03 No longer require demos to be passed into demo
2024-11-03 Fix formatting
    isort and black are disagreeing and I don't have the time to figure
    out why.
2024-11-05 Fix bug with N key being put on the system queue
2024-12-17 Initial drawing and sprites for dino run
2024-12-17 Jumping seems to be working
2024-12-18 Correct refactoring for classes
2024-12-21 figuring out timer for jumping and running animation
2024-12-27 remove classes and added dicts for objs
2024-12-28 Dumb hack that fixes drawing for screen
2024-12-28 Pretty sure this mostly works, todo: collision refine and dynamic difficulty
2024-12-28 Auto creation of high score file if one does not exist
2024-12-28 Yeah no idea how to format at this point
2024-12-30 Dynamic difficulty added
2025-02-24 moved RPi/linux specific dependencies into its own requirements, they were breaking windows
2025-02-24 fixed linux specific python path programming, now the simulator works on windows
2025-02-25 black
2025-02-25 ran isort correctly??
2025-02-25 rearrange hw folder and add v2 pcb
2025-02-25 added firmware for v2 board
2025-04-08 committing stuff from forever ago, maybe won't work
2025-04-08 Creating pinball main
2025-05-25 gitignore update
2025-05-26 Changed simluator to add different color of digits that can be changed with a click of button.
2025-06-21 Saving to work on something else
2025-06-27 added prusa demo
2025-08-29 Update to support big screen
2025-08-29 Add presentation mode
2025-08-29 Make the demos a little tighter
2025-11-14 Fix black error
2025-11-14 Use only log files
    No longer print log messages to stderr
2025-11-14 Set default logging level to INFO
    Changed the logger_level array to start with INFO instead of ERROR,
    making INFO the default logging level when no verbose flags are used.
    This ensures users see important operational messages (including the
    ASCII art banner) without needing to pass -vvv.
    The new verbosity levels are:
    - Default (no flags): INFO
2025-11-14 fix black formatting
2025-11-15 Use pygame to play a sound
2025-11-15 Update sound demo refresh rate
    Helps with playing the sounds faster
2025-11-18 Clean up CI
    - Add new Python version
    - Remove Pi runner until it is ready...
2025-11-21 Fix address and debug demo added
2025-12-06 Bump urllib3 from 2.5.0 to 2.6.0
    Bumps [urllib3](https://github.com/urllib3/urllib3) from 2.5.0 to 2.6.0.
    - [Release notes](https://github.com/urllib3/urllib3/releases)
    - [Changelog](https://github.com/urllib3/urllib3/blob/main/CHANGES.rst)
    - [Commits](https://github.com/urllib3/urllib3/compare/2.5.0...2.6.0)
    ---
    updated-dependencies:
2025-12-19 Add configuration file for creating v2 display
